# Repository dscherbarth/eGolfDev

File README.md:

# eGolfDev
Development and Documentation of my electric vehicle conversion of a VW Golf

This is a work in progress, hopefully more than a dump of my current work, but it is not a turnkey build and go repo :)

Included are sources for the motor controller cpu (lpc1769), the head unit application (beagle bone black), the battery monitor (arduino) and the pic that controlls battery balance for each of the 77 lithium cells.  Also included are collected docs from the original chrysler program (motor and controller) and schematic/pcb layout for the cpu board and the balancer boards.

Initial commit of sources and pcb files

I would be happy to discuss this project:  dougsc@yahoo.com

6/8/17 Updates for latest controller tuning and new battery monitor/balancer hardware software

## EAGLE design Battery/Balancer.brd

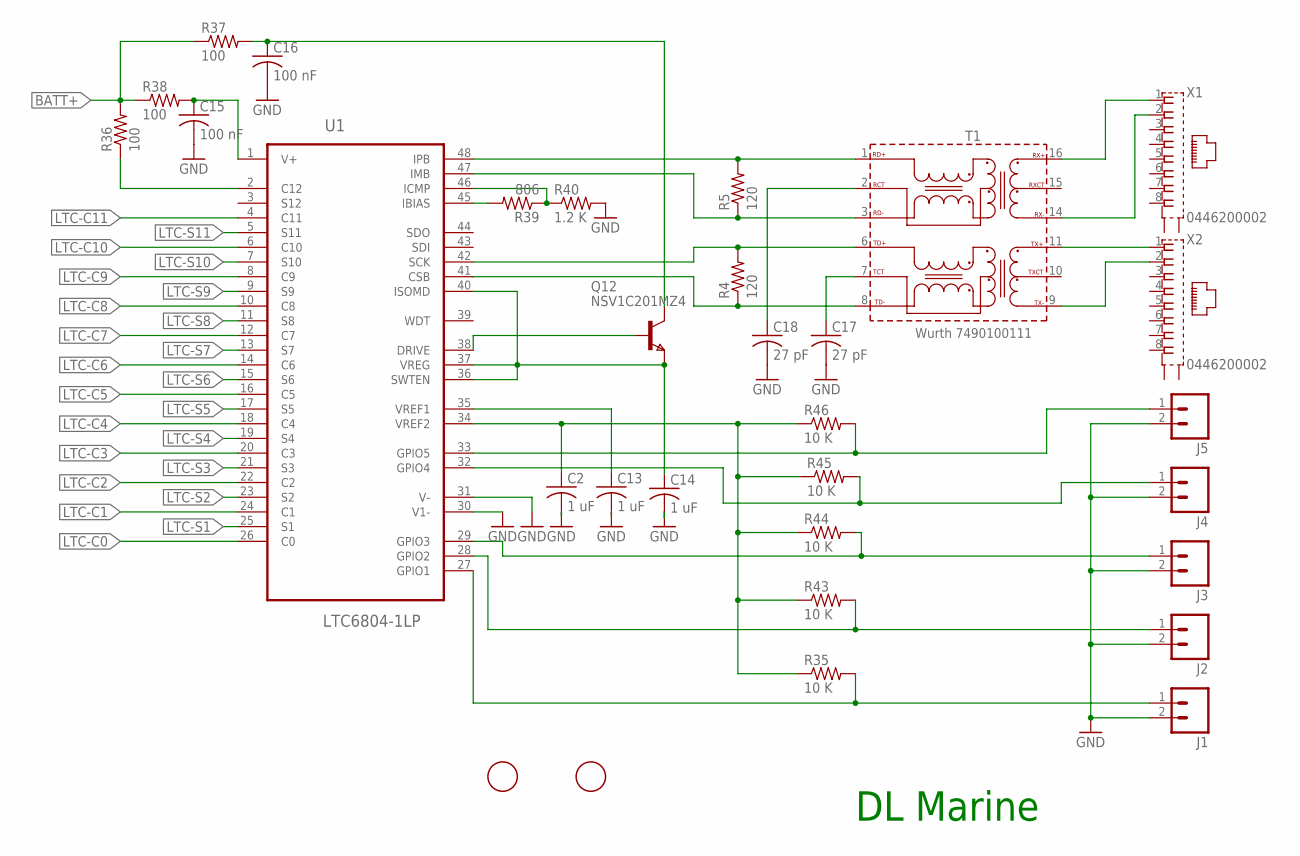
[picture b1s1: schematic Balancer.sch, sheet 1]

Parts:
C2, C13, C14: 1 uF; C0805
C15, C16: 100 nF; C0805
C17, C18: 27 pF; C0805
J1, J2, J3, J4, J5: M02PTH; 1X02
Q12: NSV1C201MZ4; SOT223
R4, R5: 120; R0805
R35, R43, R44, R45, R46: 10 K; R0805
R36, R37, R38: 100; R0805
R39: 806; R0805
R40: 1.2 K; R0805
T1: Wurth 7490100111; 749010011
U1: LTC6804-1LP; SOP50P810X110-48N
U$1, U$2: FIDUCIAL; FIDUCIAL_1MM
X1, X2: 0446200002

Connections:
BATT+: R36.2, R37.1, R38.1; also elsewhere on the board
GND: C2.2, C13.2, C14.2, C15.2, C16.2, C17.2, C18.2, J1.2, J2.2, J3.2, J4.2, J5.2, R40.2, U1.30 (V1-), U1.31 (V-); also elsewhere on the board
LTC-C0: U1.26 (C0); also elsewhere on the board
LTC-C1: U1.24 (C1); also elsewhere on the board
LTC-C2: U1.22 (C2); also elsewhere on the board
LTC-C3: U1.20 (C3); also elsewhere on the board
LTC-C4: U1.18 (C4); also elsewhere on the board
LTC-C5: U1.16 (C5); also elsewhere on the board
LTC-C6: U1.14 (C6); also elsewhere on the board
LTC-C7: U1.12 (C7); also elsewhere on the board
LTC-C8: U1.10 (C8); also elsewhere on the board
LTC-C9: U1.8 (C9); also elsewhere on the board
LTC-C10: U1.6 (C10); also elsewhere on the board
LTC-C11: U1.4 (C11); also elsewhere on the board
LTC-S1: U1.25 (S1); also elsewhere on the board
LTC-S2: U1.23 (S2); also elsewhere on the board
LTC-S3: U1.21 (S3); also elsewhere on the board
LTC-S4: U1.19 (S4); also elsewhere on the board
LTC-S5: U1.17 (S5); also elsewhere on the board
LTC-S6: U1.15 (S6); also elsewhere on the board
LTC-S7: U1.13 (S7); also elsewhere on the board
LTC-S8: U1.11 (S8); also elsewhere on the board
LTC-S9: U1.9 (S9); also elsewhere on the board
LTC-S10: U1.7 (S10); also elsewhere on the board
LTC-S11: U1.5 (S11); also elsewhere on the board
unnamed: C16.1, Q12.2 (C), Q12.4 (C), R37.2
unnamed: R5.2, T1.1 (RD+), U1.48 (IPB)
unnamed: R5.1, T1.3 (RD-), U1.47 (IMB)
unnamed: C14.1, Q12.3 (E), U1.36 (SWTEN), U1.37 (VREG), U1.40 (ISOMD)
unnamed: C13.1, U1.35 (VREF1)
unnamed: C2.1, R35.1, R43.1, R44.1, R45.1, R46.1, U1.34 (VREF2)
unnamed: R4.2, T1.6 (TD+), U1.42 (SCK)
unnamed: R4.1, T1.8 (TD-), U1.41 (CSB)
unnamed: R39.2, U1.45 (IBIAS)
unnamed: R39.1, R40.1, U1.46 (ICMP)
unnamed: C15.1, R38.2, U1.1 (V+)
unnamed: C18.1, T1.2 (RCT)
unnamed: C17.1, T1.7 (TCT)
unnamed: R36.1, U1.2 (C12)
unnamed: Q12.1 (B), U1.38 (DRIVE)
unnamed: T1.16 (RX+), X1.1
unnamed: T1.14 (RX-), X1.2
unnamed: T1.11 (TX+), X2.1
unnamed: T1.9 (TX-), X2.2
unnamed: J2.1, R43.2, U1.28 (GPIO2)
unnamed: J1.1, R35.2, U1.27 (GPIO1)
unnamed: J3.1, R44.2, U1.29 (GPIO3)
unnamed: J4.1, R45.2, U1.32 (GPIO4)
unnamed: J5.1, R46.2, U1.33 (GPIO5)

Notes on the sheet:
DL Marine

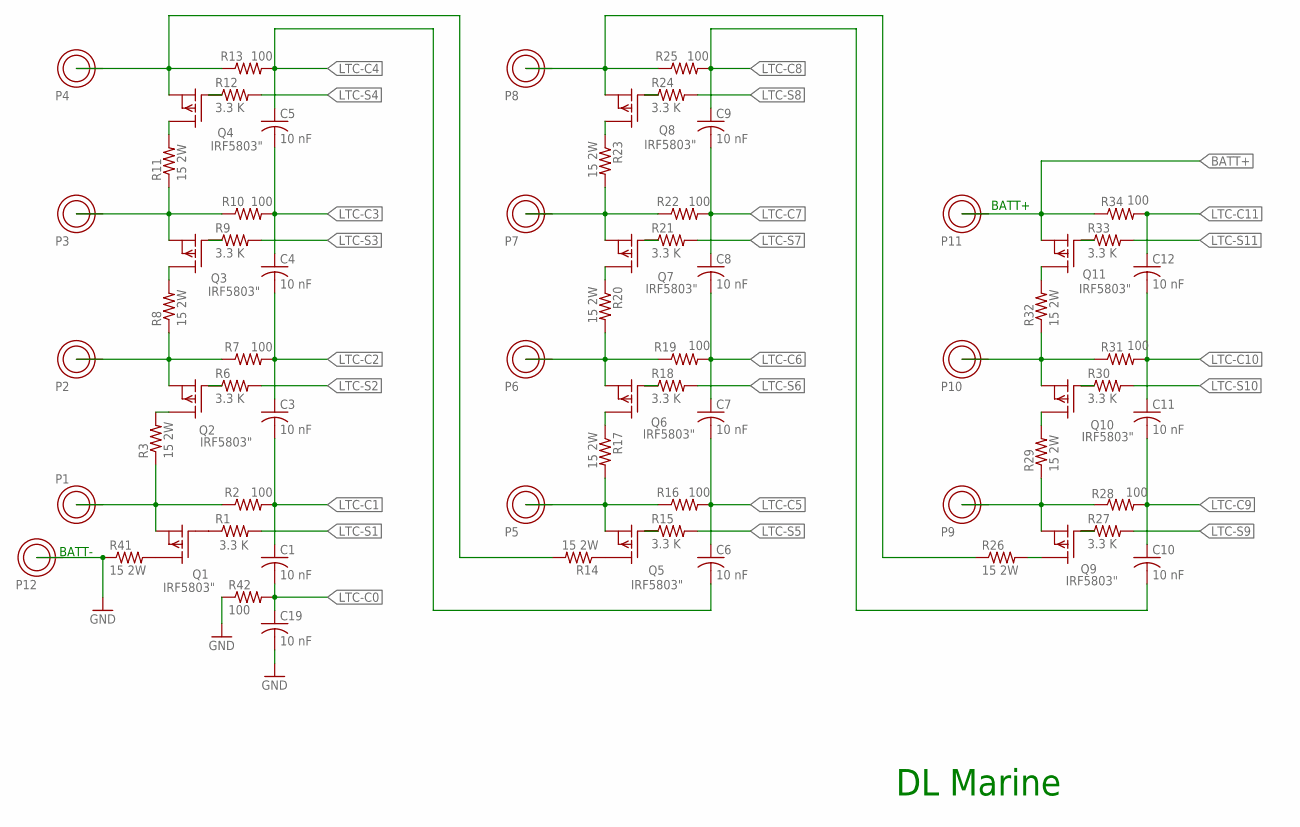
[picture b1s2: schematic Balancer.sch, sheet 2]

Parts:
C1, C3, C4, C5, C6, C7, C8, C9, C10, C11, C12, C19: 10 nF; C0805
P1, P2, P3, P4, P5, P6, P7, P8, P9, P10, P11, P12: CONN-CELL
Q1, Q2, Q3, Q4, Q5, Q6, Q7, Q8, Q9, Q10, Q11: IRF5803"; TSOP6_SOT457
R1, R6, R9, R12, R15, R18, R21, R24, R27, R30, R33: 3.3 K; R0805
R2, R7, R10, R13, R16, R19, R22, R25, R28, R31, R34, R42: 100; R0805
R3, R8, R11, R14, R17, R20, R23, R26, R29, R32, R41: 15 2W; R2512L

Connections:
BATT+: P11.P$1, Q11.P$4 (S), R34.1; also elsewhere on the board
GND: C19.2, P12.P$1, R41.1, R42.1; also elsewhere on the board
LTC-C0: C1.2, C19.1, R42.2; also elsewhere on the board
LTC-C1: C1.1, C3.2, R2.2; also elsewhere on the board
LTC-C2: C3.1, C4.2, R7.2; also elsewhere on the board
LTC-C3: C4.1, C5.2, R10.2; also elsewhere on the board
LTC-C4: C5.1, C6.2, R13.2; also elsewhere on the board
LTC-C5: C6.1, C7.2, R16.2; also elsewhere on the board
LTC-C6: C7.1, C8.2, R19.2; also elsewhere on the board
LTC-C7: C8.1, C9.2, R22.2; also elsewhere on the board
LTC-C8: C9.1, C10.2, R25.2; also elsewhere on the board
LTC-C9: C10.1, C11.2, R28.2; also elsewhere on the board
LTC-C10: C11.1, C12.2, R31.2; also elsewhere on the board
LTC-C11: C12.1, R34.2; also elsewhere on the board
LTC-S1: R1.2; also elsewhere on the board
LTC-S2: R6.2; also elsewhere on the board
LTC-S3: R9.2; also elsewhere on the board
LTC-S4: R12.2; also elsewhere on the board
LTC-S5: R15.2; also elsewhere on the board
LTC-S6: R18.2; also elsewhere on the board
LTC-S7: R21.2; also elsewhere on the board
LTC-S8: R24.2; also elsewhere on the board
LTC-S9: R27.2; also elsewhere on the board
LTC-S10: R30.2; also elsewhere on the board
LTC-S11: R33.2; also elsewhere on the board
unnamed: Q2.P$3 (G), R6.1
unnamed: Q1.P$3 (G), R1.1
unnamed: P2.P$1, Q2.P$4 (S), R7.1, R8.1
unnamed: P1.P$1, Q1.P$4 (S), R2.1, R3.1
unnamed: Q1.P$1 (D), Q1.P$2 (D), Q1.P$5 (D), Q1.P$6 (D), R41.2
unnamed: Q2.P$1 (D), Q2.P$2 (D), Q2.P$5 (D), Q2.P$6 (D), R3.2
unnamed: Q3.P$3 (G), R9.1
unnamed: P3.P$1, Q3.P$4 (S), R10.1, R11.1
unnamed: Q3.P$1 (D), Q3.P$2 (D), Q3.P$5 (D), Q3.P$6 (D), R8.2
unnamed: Q4.P$3 (G), R12.1
unnamed: P4.P$1, Q4.P$4 (S), R13.1, R14.2
unnamed: Q4.P$1 (D), Q4.P$2 (D), Q4.P$5 (D), Q4.P$6 (D), R11.2
unnamed: Q5.P$3 (G), R15.1
unnamed: P5.P$1, Q5.P$4 (S), R16.1, R17.2
unnamed: Q5.P$1 (D), Q5.P$2 (D), Q5.P$5 (D), Q5.P$6 (D), R14.1
unnamed: Q6.P$3 (G), R18.1
unnamed: P6.P$1, Q6.P$4 (S), R19.1, R20.2
unnamed: Q6.P$1 (D), Q6.P$2 (D), Q6.P$5 (D), Q6.P$6 (D), R17.1
unnamed: Q7.P$3 (G), R21.1
unnamed: P7.P$1, Q7.P$4 (S), R22.1, R23.2
unnamed: Q7.P$1 (D), Q7.P$2 (D), Q7.P$5 (D), Q7.P$6 (D), R20.1
unnamed: Q8.P$3 (G), R24.1
unnamed: P8.P$1, Q8.P$4 (S), R25.1, R26.1
unnamed: Q8.P$1 (D), Q8.P$2 (D), Q8.P$5 (D), Q8.P$6 (D), R23.1
unnamed: Q9.P$3 (G), R27.1
unnamed: P9.P$1, Q9.P$4 (S), R28.1, R29.1
unnamed: Q9.P$1 (D), Q9.P$2 (D), Q9.P$5 (D), Q9.P$6 (D), R26.2
unnamed: Q10.P$3 (G), R30.1
unnamed: P10.P$1, Q10.P$4 (S), R31.1, R32.1
unnamed: Q10.P$1 (D), Q10.P$2 (D), Q10.P$5 (D), Q10.P$6 (D), R29.2
unnamed: Q11.P$3 (G), R33.1
unnamed: Q11.P$1 (D), Q11.P$2 (D), Q11.P$5 (D), Q11.P$6 (D), R32.2

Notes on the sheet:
BATT-
BATT+
DL Marine

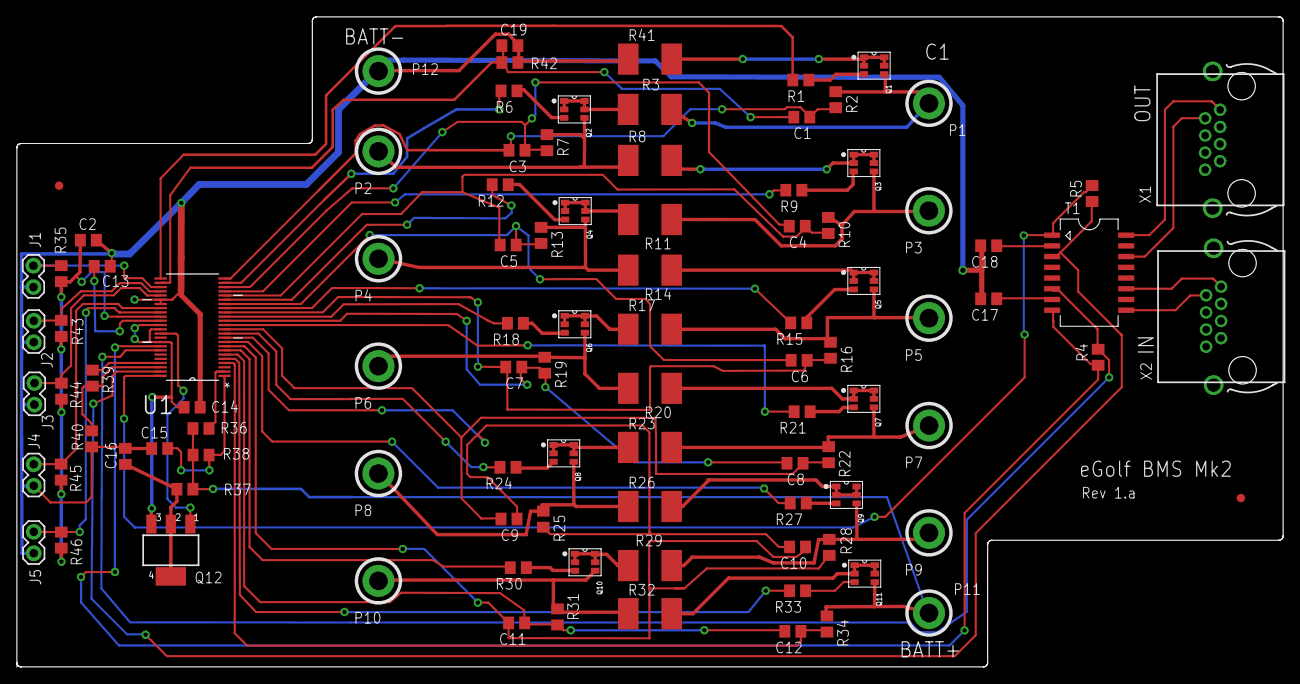
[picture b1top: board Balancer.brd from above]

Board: 2 copper layers, 150.0 x 77.0 mm, 100 parts (0 on the bottom side), 81 nets.

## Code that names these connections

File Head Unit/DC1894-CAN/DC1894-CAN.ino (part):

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 
 |  aux_codes[0][0]| aux_codes[0][1] |  aux_codes[0][2]|  aux_codes[0][3]|  aux_codes[0][4]|  aux_codes[0][5]| aux_codes[1][0] |aux_codes[1][1]|  .....    |
 |-----------------|-----------------|-----------------|-----------------|-----------------|-----------------|-----------------|---------------|-----------|
 |IC1 GPIO1        |IC1 GPIO2        |IC1 GPIO3        |IC1 GPIO4        |IC1 GPIO5        |IC1 Vref2        |IC2 GPIO1        |IC2 GPIO2      |  .....    |
*/

uint8_t tx_cfg[TOTAL_IC][6];
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
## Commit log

2015-10-29 Initial Add
2015-10-30 Notebook re-scan
2017-06-06 Add files via upload
    LTC6804-1 based balancer board and schematic
2017-06-09 Add files via upload
    use the correct variable for low volts calc
2018-03-30 New rpi head unit
2019-02-16 heater/transistor cooler code

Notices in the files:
parts and their libraries:
SparkFun-Connectors: Licensing: Creative Commons ShareAlike 4.0 International - https://creativecommons.org/licenses/by-sa/4.0
